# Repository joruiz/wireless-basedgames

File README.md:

wireless-basedgames
===================

Wireless base for the THOFU project

  This work has been supported by project grant CEN-20101019 (THOFU), funded
by the Spanish Centro para el Desarrollo Tecnol ogico Industrial (CDTI) and
supported by the Spanish Ministerio de Economía y Competitividad.

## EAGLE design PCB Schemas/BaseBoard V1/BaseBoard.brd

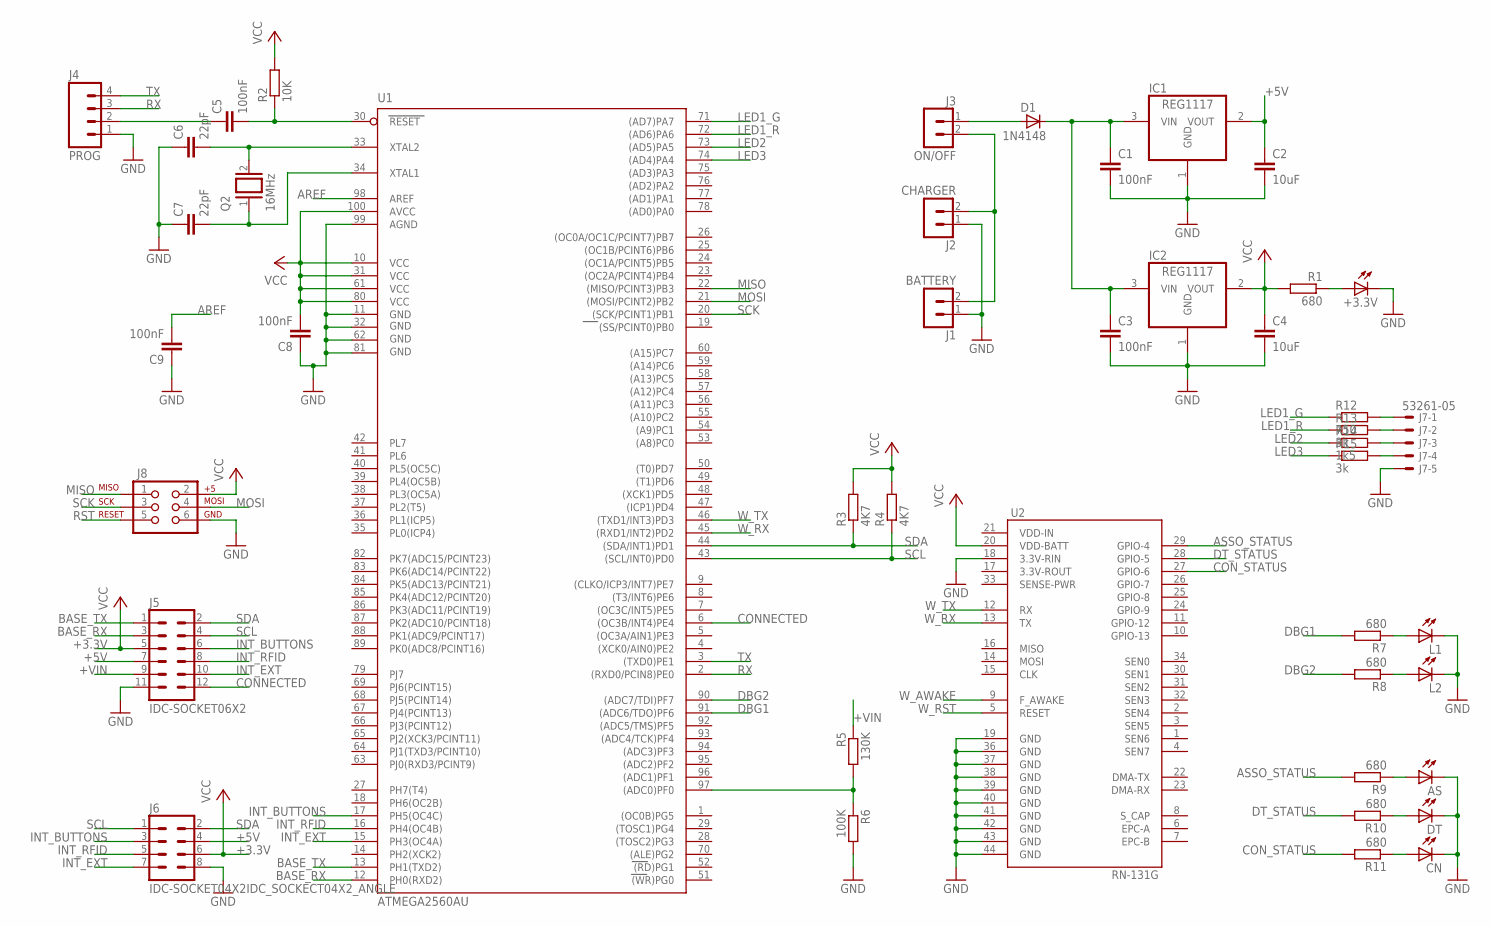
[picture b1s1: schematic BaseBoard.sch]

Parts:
+3.3V: LEDSML0805; SML0805
AS: LEDSML0805; SML0805
C1, C3, C5, C8, C9: 100nF; C0805
C2, C4: 10uF; C0805
C6, C7: 22pF; C0805
CN: LEDSML0805; SML0805
D1: 1N4148; D0805
DT: LEDSML0805; SML0805
IC1, IC2: REG1117; SOT223
J1: BATTERY; CON_2P_SMD
J2: CHARGER; CON_2P_SMD
J3: ON/OFF; CON_2P_SMD
J4: PROG; 1X04
J5: IDC-SOCKET06X2; SOCKET06X2
J6: IDC-SOCKET04X2IDC_SOCKECT04X2_ANGLE; SOCKET04X2_ANGLE
J7: 53261-05
J8: AVR_SPI_PRG_6NS; 2X3-NS
L1, L2: LEDSML0805; SML0805
Q2: 16MHz; QS
R1, R7, R8, R9, R10, R11: 680; R0805
R2: 10K; R0805
R3, R4: 4K7; R0805
R5: 130K; R0805
R6: 100K; R0805
R12: 750; R0805
R13, R15: 3k; R0805
R14: 1k5; R0805
U1: ATMEGA2560AU; TQFP100
U2: RN-131G

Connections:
+5V: C2.1, IC1.2 (VOUT), J5.7, J6.4
+VIN: C1.1, C3.1, D1.C, IC1.3 (VIN), IC2.3 (VIN), J5.9, R5.1
AREF: C9.2, U1.98 (AREF)
ASSO_STATUS: R9.2, U2.29 (GPIO-4)
BASE_RX: J5.3, U1.12 (PH0(RXD2))
BASE_TX: J5.1, U1.13 (PH1(TXD2))
BAT: R5.2, R6.1, U1.97 ((ADC0)PF0)
CONNECTED: J5.12, U1.6 ((OC3B/INT4)PE4)
CON_STATUS: R11.2, U2.27 (GPIO-6)
DBG1: R7.2, U1.91 ((ADC6/TDO)PF6)
DBG2: R8.2, U1.90 ((ADC7/TDI)PF7)
DT_STATUS: R10.2, U2.28 (GPIO-5)
GND: +3.3V.C, AS.C, C1.2, C2.2, C3.2, C4.2, C6.1, C7.1, C8.1, C9.1, CN.C, DT.C, IC1.1 (GND), IC2.1 (GND), J1.1, J2.1, J4.1, J5.11, J6.8, J7.5, J8.6, L1.C, L2.C, R6.2, U1.11 (GND), U1.32 (GND1), U1.62 (GND2), U1.81 (GND3), U1.99 (AGND), U2.18 (3.3V-RIN), U2.19 (GND), U2.36 (GND), U2.37 (GND), U2.38 (GND), U2.39 (GND), U2.40 (GND), U2.41 (GND), U2.42 (GND), U2.43 (GND), U2.44 (GND)
INT_BUTTONS: J5.6, J6.3, U1.17 (PH5(OC4C))
INT_EXT: J5.10, J6.7, U1.15 (PH3(OC4A))
INT_RFID: J5.8, J6.5, U1.16 (PH4(OC4B))
LED1_G: R12.1, U1.71 ((AD7)PA7)
LED1_R: R13.1, U1.72 ((AD6)PA6)
LED2: R14.1, U1.73 ((AD5)PA5)
LED3: R15.1, U1.74 ((AD4)PA4)
MISO: J8.1, U1.22 ((MISO/PCINT3)PB3)
MOSI: J8.4, U1.21 ((MOSI/PCINT2)PB2)
unnamed: AS.A, R9.1
unnamed: D1.A, J3.1
unnamed: J1.2, J2.2, J3.2
unnamed: DT.A, R10.1
unnamed: C5.1, J4.2
unnamed: J7.1, R12.2
unnamed: C7.2, Q2.1, U1.34 (XTAL1)
unnamed: C6.2, Q2.2, U1.33 (XTAL2)
unnamed: CN.A, R11.1
unnamed: +3.3V.A, R1.1
unnamed: J7.2, R13.2
unnamed: J7.3, R14.2
unnamed: J7.4, R15.2
unnamed: L1.A, R7.1
unnamed: L2.A, R8.1
RST: C5.2, J8.5, R2.1, U1.30 (RESET)
RX: J4.3, U1.2 ((RXD0/PCIN8)PE0)
SCK: J8.3, U1.20 ((SCK/PCINT1)PB1)
SCL: J5.4, J6.1, R4.1, U1.43 ((SCL/INT0)PD0)
SDA: J5.2, J6.2, R3.1, U1.44 ((SDA/INT1)PD1)
TX: J4.4, U1.3 ((TXD0)PE1)
VCC: C4.1, C8.2, IC2.2 (VOUT), J5.5, J6.6, J8.2, R1.2, R2.2, R3.2, R4.2, U1.10 (VCC), U1.31 (VCC1), U1.61 (VCC2), U1.80 (VCC3), U1.100 (AVCC), U2.20 (VDD-BATT)
W_AWAKE: U2.9 (F_AWAKE)
W_RST: U2.5 (RESET)
W_RX: U1.45 ((RXD1/INT2)PD2), U2.13 (TX)
W_TX: U1.46 ((TXD1/INT3)PD3), U2.12 (RX)

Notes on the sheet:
+3.3V

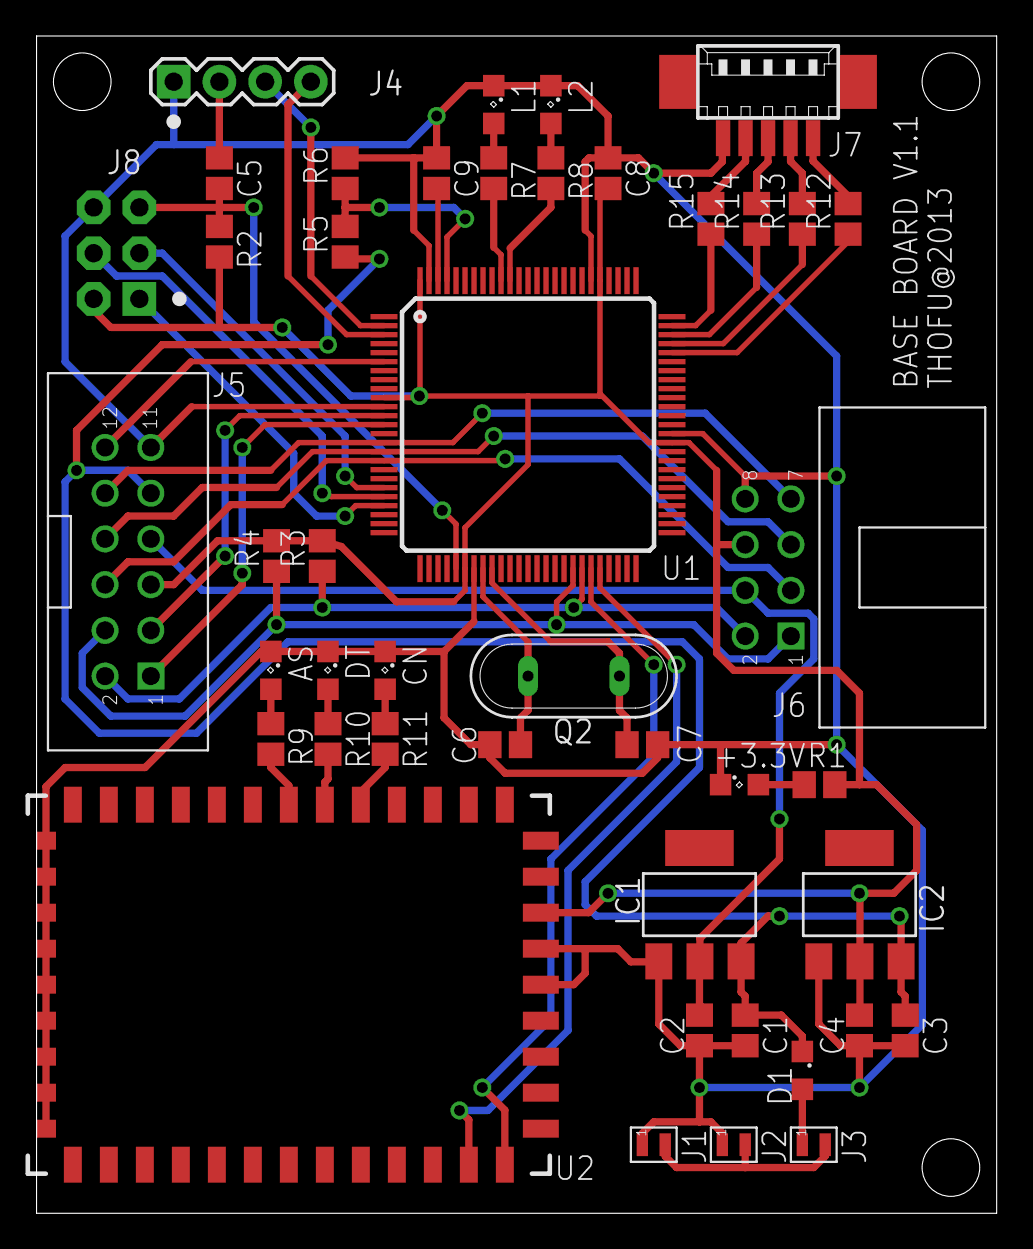
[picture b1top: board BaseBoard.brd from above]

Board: 2 copper layers, 53.3 x 65.4 mm, 44 parts (0 on the bottom side), 46 nets.

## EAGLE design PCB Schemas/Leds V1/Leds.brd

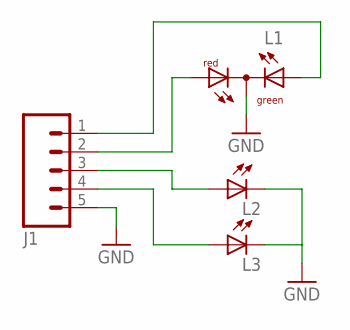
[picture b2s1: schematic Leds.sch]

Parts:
J1: M05PTH; 1X05
L1: DUOLED-RG-C; DUOLED-C-5MM
L2, L3: LED3MM

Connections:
GND: J1.5, L1.C, L2.K (C), L3.K (C)
unnamed: J1.1, L1.AX (AG)
unnamed: J1.2, L1.AR
unnamed: J1.3, L2.A
unnamed: J1.4, L3.A

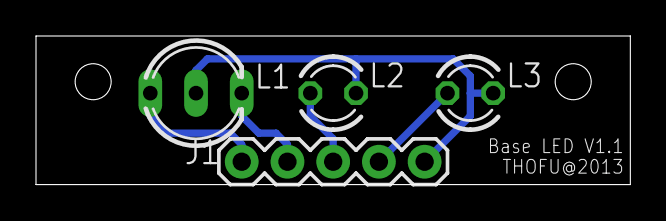
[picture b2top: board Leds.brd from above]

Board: 2 copper layers, 33.0 x 8.3 mm, 4 parts (0 on the bottom side), 5 nets.

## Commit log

2014-09-16 Finalized Version 1

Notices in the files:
parts and their libraries:
SparkFun-DigitalIC: Licensing: CC v3.0 Share-Alike You are welcome to use this library for commercial purposes.
